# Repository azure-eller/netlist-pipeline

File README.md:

# netlist-pipeline

A KiCad schematic goes in. A fabrication-ready board comes out: placed by search, routed,
scored by a physics judge, verified by KiCad's own design-rule check, exported as Gerbers.
Every stage is a recorded job with a tool version, input hash and output hash, so any run can
be replayed. The judge is a slot: a learned physics model replaces the closed-form reference
behind one HTTP contract, and a golden set decides whether the worker accepts it.

## Architecture

```mermaid
flowchart LR
    client([client]) -->|POST /designs| api[api<br/>FastAPI]
    api --> pg[(Postgres<br/>designs, runs, jobs,<br/>stages, nets, candidates,<br/>verifications, artifacts)]
    api --> s3[(S3<br/>uploads, boards,<br/>reports, gerbers)]
    worker[worker<br/>kicad-cli, pcbnew,<br/>Freerouting] -->|claim job<br/>SKIP LOCKED| pg
    worker --> s3
    client -->|GET /runs/id| api
```

Two containers from one image, a managed Postgres, and a bucket. The API never does work that
takes more than a second: it writes a job row and the worker claims it. The worker runs the
eight stages one job at a time, and the judge stage calls a separate judge service over HTTP.
That service is the model slot.

<details>
<summary>Detailed architecture</summary>

</details>

**Stage 4, watched.** `GET /` on the API is a status board: one row per run, one cell per
stage, and while a run is in `place` it draws the annealer live, parts, rat's nest by net
class and the cost curve, from snapshots the stage writes every 0.1 % of its moves.

## The judge, and the physics model inside it

Everything in this section is about one question: **is this board electrically good?** A board
can have every wire connected and still be bad. This is what the judge measures, why part of
it had to be learned, and how we know the learned part is right.

### 1. What the judge does

After routing, the pipeline has up to ten candidate boards, all wired correctly. The judge
gives each one a score and the best one goes on to verification. The score is a penalty: zero
for a board that breaks no rule, more negative for every rule it breaks and for how badly.

| rule | in plain words | needs physics? |
|---|---|---|
| current | a power trace must be wide enough to carry its current without heating more than 10 °C | textbook formula (IPC-2221) |
| impedance | a high-speed trace must present the impedance the chip expects, 50 Ω by default, within 10 % | **yes** |
| diff pair | the two wires of a differential pair must be the same length within 1 mm | no |
| decoupling | a chip's decoupling capacitor must sit within 10 mm of the pin it serves | no |
| crosstalk | two traces must not run side by side for long stretches with a small gap | no |
| vias | a high-speed trace should change layers at most twice | no |
| unrouted | any connection the router gave up on | no |

Each broken rule costs its weight times how far past the limit it went. A 0.3 mm trace
asked to carry twice what it can costs more than one asked to carry 5 % more. Current and
impedance weigh most, because those are the ones that make a board not work rather than
merely not ideal.

The judge picks the best candidate. It never passes or fails a run; that is verify's job.

### 2. Impedance, and why it is the hard rule

Six of the seven rules are geometry you can measure with a ruler: distance, length, width,
count. Impedance is different.

A fast signal on a trace does not behave like water in a pipe, it behaves like a wave on a
rope. The trace has a characteristic impedance, measured in ohms, and if the chip at the far
end expects 50 Ω and the trace is 90 Ω, part of every edge bounces back and the signal is
corrupted. The impedance is set by four things: how wide the trace is (**w**), how far it sits
above the copper ground plane (**h**), how thick the copper is (**t**), and how strongly the
board material stores electric field, a number called relative permittivity (**er**, about
4.5 for ordinary FR-4 fibreglass). Wider or closer to the plane means lower impedance.

The judge needs this number for every high-speed trace on every candidate. So where does it
come from? That is a separate piece, the **physics provider**, and there are three of them.

### 3. Three ways to get the number

| provider | what it is | one answer takes |
|---|---|---|
| formula | the IPC-2141 closed form, a one-line equation from a standards handbook | a few microseconds |
| field solver | our own program that computes the electric field around the trace, alone or among its neighbours | 0.4 to 1.6 s |
| learned-fd v5 | gradient boosting trained to predict what the solver says for one trace over a plane | under a millisecond |
| learned-cut v8 | a small transformer that reads the whole slice, neighbours and all, and predicts the solver's capacitance matrix | a few milliseconds |

The same three traces through all three, single-ended impedance in ohms:

| trace | formula | field solver | learned-fd v5 |
|---|---|---|---|
| 0.2 mm wide, 1.51 mm above the plane (a signal trace on a plain 2-layer board) | 137.3 | 135.7 | 134.1 |
| 2.9 mm wide, same board (what 50 Ω needs on that board) | 48.1 | 49.1 | 49.1 |
| 0.35 mm wide, 0.2 mm above the plane (a 4-layer board) | 49.0 | 51.4 | 53.0 |

The first row is the finding from run 76: the I2C traces on the generated Raspberry Pi HAT are
0.2 mm wide over a 1.5 mm core, so they sit near 135 Ω against a 50 Ω target, and the judge
flagged both of them.

The formula is quick and usually close, but it is a curve fitted to measurements decades
ago, valid over a limited range of shapes, and it knows nothing about a neighbouring trace or
a missing plane. The field solver is the truth we have. The learned models exist because the
truth is slow.

The first three describe a slice with four numbers and assume a solid plane under the trace.
Boards this pipeline generates have no plane, and only 46 of the 5,206 slices cut from our
real boards do. The fourth provider reads the slice as it is: a list of conductors, each
with its width and distance, and whether a plane is there. Each conductor becomes a token, the
tokens attend to each other with their pairwise gaps built into the attention, and a
symmetric head reads off the full capacitance matrix, the object the solver itself computes.
Impedance and crosstalk coupling are derived from that matrix by the solver's own formula.
Trained on 8,000 synthetic slices plus the real slices of one board family, it predicts the
solver within 1.8 % on a board family it never saw, where gradient boosting on hand-made
features manages 3.5 %. The record, including the run that did not transfer, is in
[docs/experiments/cutnet.md](docs/experiments/cutnet.md).

### 4. The field solver, in plain words

"2D" means the solver never looks at the whole board. Impedance does not depend on how long a
trace is, only on its cross-section, so the solver takes one slice straight across the trace
and works entirely on that slice.

What happens on the slice:

1. **Divide it into a grid.** About 400 cells across and 200 up. Cells are small near the
   trace, where the field changes quickly, and grow larger out towards the edges where
   nothing much happens.
2. **Pin the known voltages.** The trace is held at 1 volt, the ground plane at 0.
3. **Find the voltage everywhere else.** In empty space, each point's voltage is the average of
   its neighbours; at the boundary between air and board material, the average is weighted by
   permittivity. That gives one equation per grid point, about 80,000 of them, all coupled.
   The solver writes them as one sparse matrix and solves it in one shot. The right panel
   above is the result: every grid point's voltage.
4. **Turn the field into capacitance.** A field stores energy, and the energy stored per metre
   of trace tells you the capacitance per metre between trace and plane.
5. **Do it twice.** Once with the real board material and once with the board replaced by air.
   Impedance is set by the two capacitances together, and that pair also gives the speed the
   signal travels at.

For a pair of traces it does the same with the second trace held at +1 V and then at −1 V,
which is what differential pairs and crosstalk need.

The solver was checked against the Hammerstad-Jensen equations, the most trusted closed form
for this shape, and its impedance agrees within 1 % across the range where that form is valid. It takes
about 0.4 s per slice. A board with a dozen high-speed nets, ten candidates, and a search
that wants to score thousands of layouts cannot afford that.

### 5. Teaching a model to imitate the solver

The pattern is: a slow, trusted source of answers produces a dataset; a fast model learns it;
the fast model is checked against the slow one before it is allowed near a real board.

**The dataset.** 5,000 random cross-sections were drawn from the ranges real boards use, and
the solver answered every one. The draws are logarithmic, so thin traces and thin dielectrics,
where impedance changes fastest, are not starved of examples.

| input | range |
|---|---|
| trace width w | 0.1 to 2.0 mm |
| height above plane h | 0.08 to 1.6 mm |
| copper thickness t | 0.018, 0.035 or 0.070 mm, the three foils fabs stock |
| permittivity er | 3.0 to 4.8 |
| gap to a partner trace s | 0.1 to 3.0 mm, present in half the samples |

The work went through the same job queue that builds boards: four jobs of 1,250 slices each,
about two minutes per job on 16 cores. The result is dataset 17: four files plus a manifest
naming the sampler version, solver version and random seed, with the sha256 of every file. The
random seed means the exact same 5,000 slices can be regenerated from scratch.

**The model.** Gradient boosting: 600 small decision trees, each one trained to correct the
mistakes of all the trees before it. The inputs are the four (or five) numbers above, given
to the trees as logarithms, because impedance behaves logarithmically in width and height and
that makes the job easier. There are two models in the artifact: one for single traces
predicting z0, one for pairs predicting the odd- and even-mode impedances that differential
pairs and crosstalk are built from. Training plus the check below took 81 s.

**The first check.** 20 % of the dataset was held back from training and scored afterwards:
0.9 % average error on single-trace impedance. Then 200 brand-new slices were drawn after
training was finished and solved by the solver, so the model was tested on data that did not
exist when it was built:

| target | average error | 95th percentile |
|---|---|---|
| z0, single trace | 0.9 % | 2.4 % |
| z_odd, pair | 2.1 % | 4.2 % |
| z_even, pair | 1.7 % | 3.6 % |

The judge's impedance rule allows 10 %, so the model's error is a small fraction of the
tolerance it is judging against.

### 6. The gate: no model touches a board until it passes

Agreeing with the solver on random slices is not the same as agreeing on real boards. So
every judge version, the formula included, has to pass the **golden set** before the worker
will accept it: seven real boards with known verdicts. Two are deliberately broken copies of
the others, one with a capacitor moved 30 mm so it sits 93 mm from the pin it serves, and one with every +5V trace
thinned to 0.15 mm, and a judge must rank each broken board below its original. Two more
carry high-speed traces with copper, so the impedance rule is actually exercised. The expected
answers come from the field solver.

Three earlier learned judges, v2 through v4, were refused at this gate. They matched the
reference on the ordinary boards and under-penalised the far-capacitor board. They never
reached the worker. The record is in [docs/experiments](docs/experiments/README.md).

Passing writes a row in the `judge_approvals` table naming the judge's name, version, the
sha256 of its model file, and the sha256 of the golden set it passed. The `models` table
already holds the file's location, its dataset, its feature encoding, the library version and
the commit. Neither table can be edited, only added to. Then:

- the judge service loads the model file from S3, hashes the bytes, and refuses to start if the
  hash differs from the row;
- the worker's judge stage asks the service who it is and refuses the run unless that exact
  (name, version, file hash) has an approval row;
- every score the pipeline stores records which bytes produced it.

Swapping a model file, retraining under the same version number, or pointing the worker at an
unapproved judge all fail loudly.

### 7. What it does not know

- **One slice, one layer.** The general solver sees every conductor on the trace's own
  layer and a plane on the next, but not a trace on another layer, vias, or a plane with a
  hole in it. Boards this pipeline generates still have no ground pour, which is why the
  golden answer key had to be recomputed with real slices and why the formula and v5 now
  fail it.
- **No losses, no length.** Copper resistance and dielectric loss are ignored, and nothing
  depends on how long a trace is.
- **Only inside the box.** The model was trained on the ranges in the table above. Outside
  them it extrapolates, and the golden set is what catches that.
- **Simplified rules.** The judge charges nothing for total wire length; [docs/EVAL.md](docs/EVAL.md)
  shows search beating the human layout on this judge while using 73 % more copper.

[docs/FACTORY.md](docs/FACTORY.md) is the plan for the next step: labels from real board
geometry instead of random slices, so a model can learn what a neighbouring trace or a
missing plane does.

## Run it

```
make up && make migrate        # Postgres + MinIO
make api                       # FastAPI on :8000; GET / is a status board: runs, stages, the annealer live
make worker                    # the job loop
make demo                      # upload pic_programmer, poll, print the report
make check                     # ruff, mypy strict, unit tests, end-to-end suite
curl -F file=@project.zip 'http://localhost:8000/designs?mode=generate&seeds=3'
```

Needs KiCad 10 and Freerouting locally, or the Dockerfile. Live at
https://netlist-api-ivqr.onrender.com/healthz. Details in [docs/DEPLOY.md](docs/DEPLOY.md).

## Go deeper

- [SPEC.md](SPEC.md): the contract. Stages, constraints format, judge contract, invariants.
- [docs/JUDGE.md](docs/JUDGE.md): the judge slot, the approval gate, the field-solver oracle
  and the learned surrogate that passed it.
- [docs/FACTORY.md](docs/FACTORY.md): where a geometry model's labels would come from.
- [docs/EVAL.md](docs/EVAL.md): search versus the human layout on the fixtures.
- [docs/DECISIONS.md](docs/DECISIONS.md): what was not built and why. No language model runs
  in the pipeline; Claude built the repo.
- [docs/experiments](docs/experiments/README.md): every judge and placer experiment, with
  the ones that failed.

## How work gets done here

Cards on the Linear board labelled `agent` are picked up by OpenHands, self-hosted on
the lab machine, in a container built from this repo's image; the result is a pull
request with the link back on the card. This repo provides only `AGENTS.md` (the rules every
agent reads) and `make sandbox-image`; the lane itself, what was bought and what was built, and
why research is run differently are in the separate
[agent-lane](https://github.com/azure-eller/agent-lane) repo.

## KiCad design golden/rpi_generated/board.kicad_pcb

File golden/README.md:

# Golden set

Boards with expected scorecards for gating judge versions (SPEC.md, "Judge versions and
approval"). Built by `scripts/golden.py --capture` from local runs; rerunning overwrites.
`expected.json` is the rule judge's answer (regression and disagreement, not ground truth).

| case | board | netlist / constraints | expected (rules 0.1.0) |
|---|---|---|---|
| `pic_human` | `tests/fixtures/pic_programmer/pic_programmer.kicad_pcb`, the human layout | latest local judge-mode run of pic_programmer | -6.48; 3 decoupling (C1 on VCC, C6 and C7 on VCC_PIC) |
| `pic_generated` | chosen candidate of local generate run 34 (3 seeds) | same as `pic_human` | -1.20; decoupling C1, current on VCC_PIC |
| `rpi_generated` | chosen candidate of local generate run 27 (rpi_hat) | run 27 | -3.43; 2 current (+5V, GND) |
| `pic_cap_far` | `pic_human` with C1 moved 30 mm right of U1 (`pcb.set_positions`) | same as `pic_human` | -16.12; same 3 decoupling, C1 now ~93 mm from the nearest VCC pin. Must score below `pic_human`. |
| `rpi_thin` | `rpi_generated` with every `+5V` segment width set to 0.15 mm (text edit) | run 27 | -4.99; same 2 current violations, +5V excess larger. Must score below `rpi_generated`. |

Note: C1 already violates decoupling in the human layout (11.8 mm from U3 pin 5 on VCC; U1
carries no VCC pad), and the one `+5V` segment on the HAT already violates current at 0.2 mm.
The two mutated cases therefore worsen an existing violation rather than adding one; the
ordering constraints are what the gate checks.

## Impedance-live cases (added 2026-09-08)

The five original cases never exercise the impedance rule: the fixtures' fast nets carry no
copper. Two cases fix that, both on the generated HAT board with its routed I2C nets declared
`high_speed`:

- `rpi_fast`: target 50 ohm. A 0.2 mm trace over 1.51 mm FR-4 is far from 50 ohm, so both
  nets violate under every provider; the score depends on the provider's z0 (oracle -20.58,
  closed form -20.88).
- `rpi_fast_tuned`: target set to the closed form's own answer for that geometry. The formula
  passes by construction; the oracle passes only if its z0 is within 10% of the formula's,
  which it is here. A surrogate that drifts fails this case first.

Expected answers for every case now come from the oracle (`scripts/golden.py --physics
oracle --update`); the closed form is measured against them like any other judge and passes.

## Answer key recaptured from the general solver (2026-09-09)

`scripts/golden.py --physics oracle --update` again, now with the impedance rule asking the
provider per real cross-section (`docs/FACTORY.md` step 2: neighbours, plane or not). The five
plane-less cases did not move. The two impedance-live cases did, because the generated HAT has
no plane under its I2C traces and the old key assumed one:

| case | old key (plane assumed) | new key (real cross-sections) |
|---|---|---|
| `rpi_fast` | -20.58 | -24.18 |
| `rpi_fast_tuned` | -3.43 | -4.16 |

Any judge that still assumes a plane (the closed form, `learned-fd v5`) is measured against
this key like any other; the ledger in `docs/experiments/golden.jsonl` records what happened.

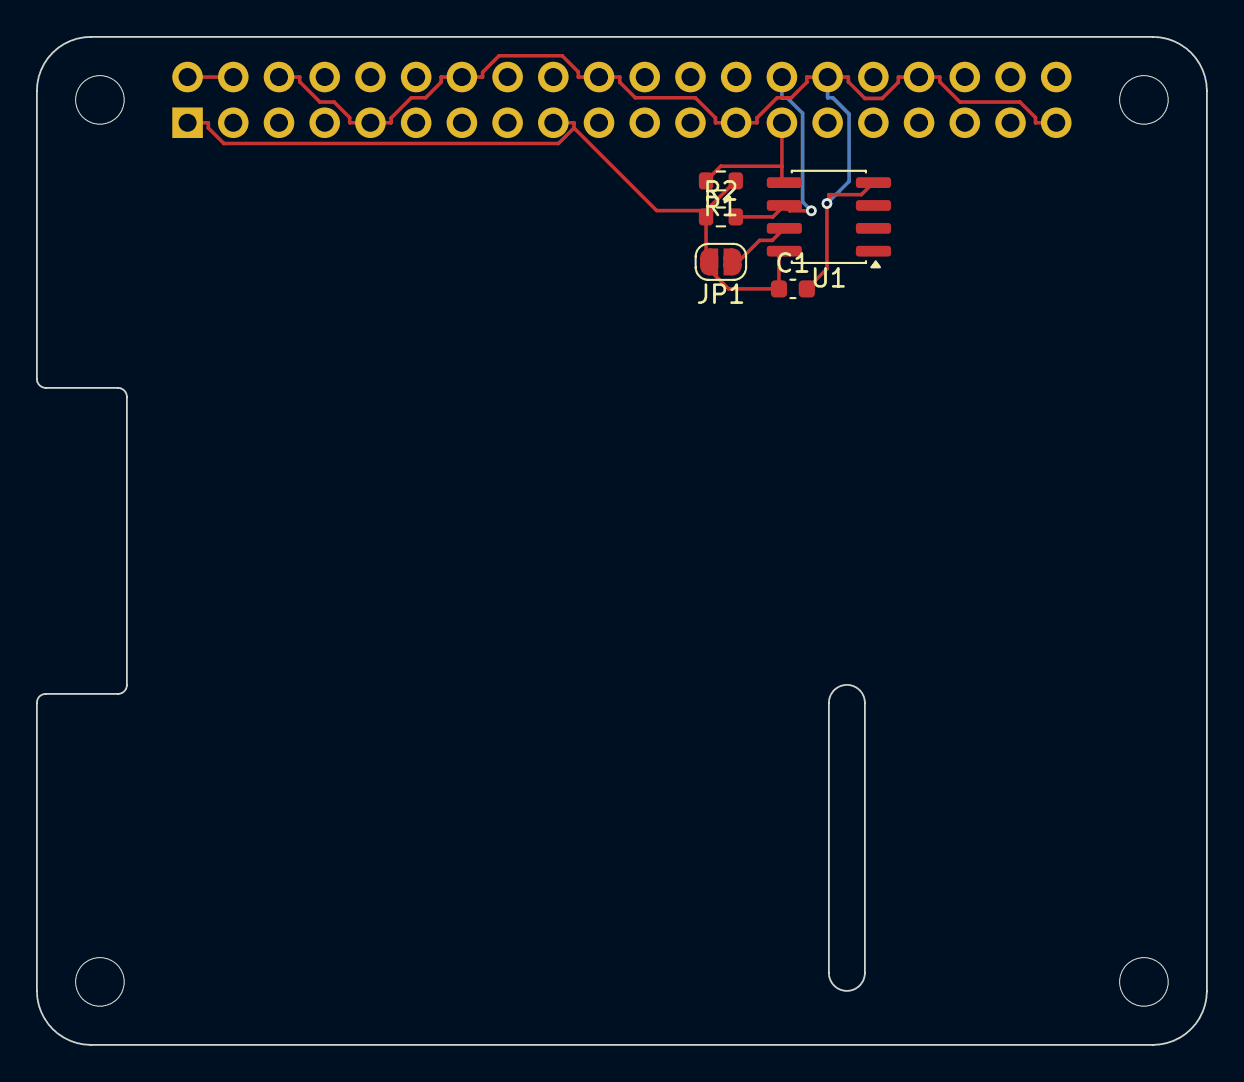
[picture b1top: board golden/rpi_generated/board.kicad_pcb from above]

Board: 2 copper layers, 65.0 x 56.0 mm, 10 parts (1 on the bottom side), 6 nets.

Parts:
C1: 100n; C_0603_1608Metric
J1: GPIO; PinSocket_2x20_P2.54mm_Vertical
JP1: ID_WP; SolderJumper-2_P1.3mm_Open_RoundedPad1.0x1.5mm
MH1, MH2, MH3, MH4: MountingHole_2.7mm_M2.5
R1, R2: 3.9k; R_0603_1608Metric
U1: CAT24C256; SOIC-8_3.9x4.9mm_P1.27mm

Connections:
+3V3: C1.1, J1.1, J1.17, JP1.2, R1.1, R2.1, U1.8
+5V: J1.2, J1.4
/ID_SCL: J1.28, R2.2, U1.6
/ID_SDA: J1.27, R1.2, U1.5
GND: C1.2, J1.6, J1.9, J1.14, J1.20, J1.25, J1.30, J1.34, J1.39, U1.4
unnamed: JP1.1, U1.7

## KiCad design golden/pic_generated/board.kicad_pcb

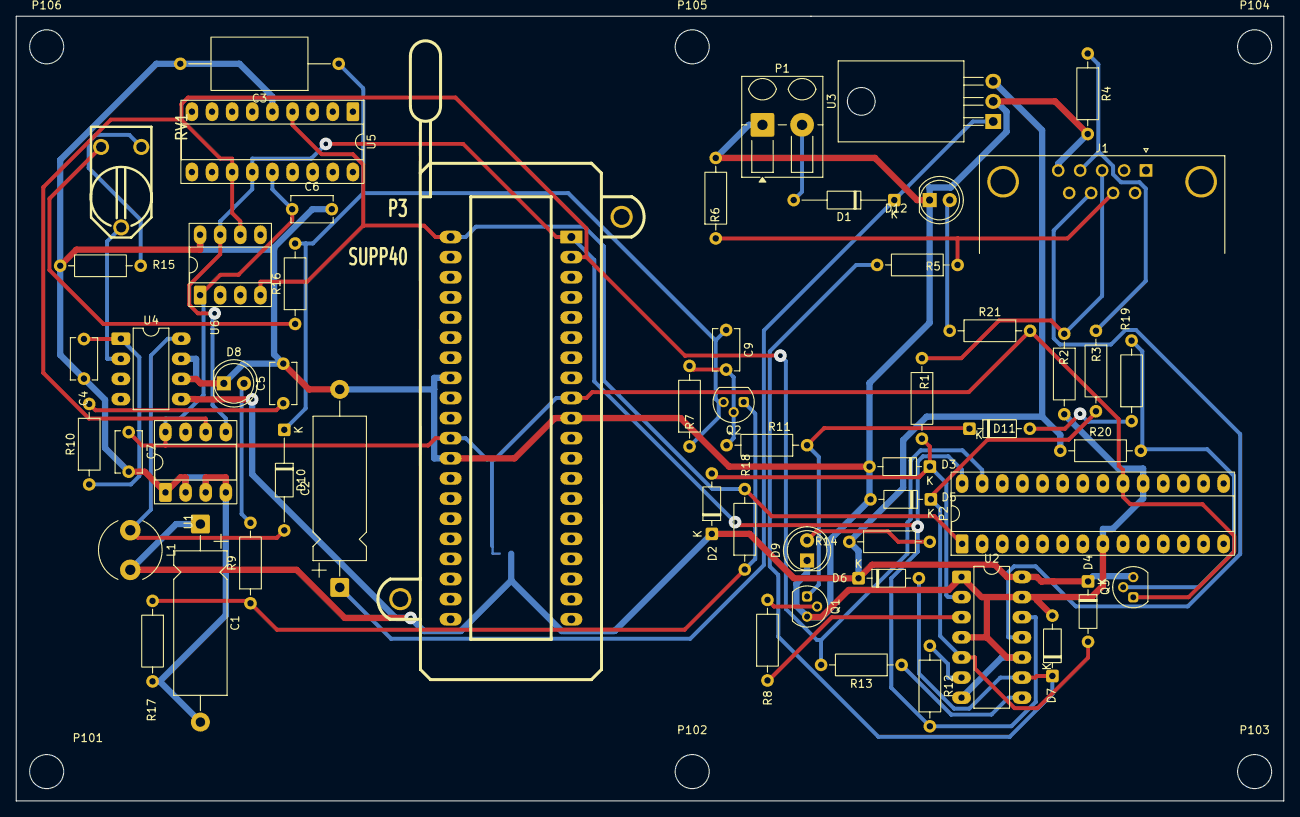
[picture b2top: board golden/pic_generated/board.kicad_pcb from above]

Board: 2 copper layers, 160.0 x 99.1 mm, 63 parts (1 on the bottom side), 34 nets.

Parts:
C1: 100µF; CP_Axial_L18.0mm_D6.5mm_P25.00mm_Horizontal
C2: 220uF; CP_Axial_L18.0mm_D6.5mm_P25.00mm_Horizontal
C3: 22uF/25V; C_Axial_L12.0mm_D6.5mm_P20.00mm_Horizontal
C4: 0; C_Disc_D5.1mm_W3.2mm_P5.00mm
C5: 10nF; C_Disc_D5.1mm_W3.2mm_P5.00mm
C6, C7: 100nF; C_Disc_D5.1mm_W3.2mm_P5.00mm
C9: 220nF; C_Disc_D5.1mm_W3.2mm_P5.00mm
D1: 1N4004; D_DO-35_SOD27_P12.70mm_Horizontal
D2, D3, D4, D5, D6, D7, D11: BAT43; D_DO-35_SOD27_P7.62mm_Horizontal
D8: RED-LED; LED_D5.0mm
D9: GREEN-LED; LED_D5.0mm
D10: SCHOTTKY; D_DO-35_SOD27_P12.70mm_Horizontal
D12: YELLOW-LED; LED_D5.0mm
J1: DB9-FEMAL; DSUB-9_Socket_Horizontal_P2.77x2.84mm_EdgePinOffset7.70mm_H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
JP1: JUMPER; SolderJumper-2_P1.3mm_Open_TrianglePad1.0x1.5mm
L1: 22uH; L_Radial_D7.8mm_P5.00mm_Fastron_07HCP
P1: CONN_2; Altech_AK300_1x02_P5.00mm_45-Degree
P2: SUPP28; DIP-28_W7.62mm_Socket_LongPads
P3: SUPP40; 40tex-Ell600
P101, P102, P103, P104, P105, P106: CONN_1; MountingHole_4.3mm_M4
Q1: BC237; TO-92
Q2, Q3: BC307; TO-92
R1, R2, R3, R4, R5, R6, R7: 10K; R_Axial_DIN0207_L6.3mm_D2.5mm_P10.16mm_Horizontal
R8: 1K; R_Axial_DIN0207_L6.3mm_D2.5mm_P10.16mm_Horizontal
R9, R19, R20: 2.2K; R_Axial_DIN0207_L6.3mm_D2.5mm_P10.16mm_Horizontal
R10: 5,1K; R_Axial_DIN0207_L6.3mm_D2.5mm_P10.16mm_Horizontal
R11, R17: 22K; R_Axial_DIN0207_L6.3mm_D2.5mm_P10.16mm_Horizontal
R12, R13, R14, R21: 470; R_Axial_DIN0207_L6.3mm_D2.5mm_P10.16mm_Horizontal
R15: 6.2K; R_Axial_DIN0207_L6.3mm_D2.5mm_P10.16mm_Horizontal
R16: 62K; R_Axial_DIN0207_L6.3mm_D2.5mm_P10.16mm_Horizontal
R18: 220; R_Axial_DIN0207_L6.3mm_D2.5mm_P10.16mm_Horizontal
RV1: 1K; RV2X4
U1: 24Cxx; DIP-8_W7.62mm_Socket_LongPads
U2: 74HC125; DIP-14_W7.62mm_LongPads
U3: 7805; TO-220-3_Horizontal_TabDown
U4: LT1373; DIP-8_W7.62mm_LongPads
U5: PIC_18_PINS; DIP-18_W7.62mm_Socket_LongPads
U6: PIC_8_PINS; DIP-8_W7.62mm_Socket_LongPads

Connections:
/CLOCK-RB6: P2.27, P3.39, R13.2, U1.6 (SCL), U5.12 (ICSPC/RB6), U6.6 (GP1)
/DATA-RB7: P2.28, P3.40, R12.2, U1.5 (SDA), U2.12, U5.13 (ICSPD/RB7), U6.7 (GP0)
/PC-CLOCK-OUT: J1.7, R5.1, R6.1
/PC-DATA-IN: J1.8, U2.11
/PC-DATA-OUT: J1.4, R3.1, R4.1
/VPP_ON: J1.3, R1.1, R2.1
/VPP/MCLR: P2.1, P3.1, R18.2, U5.4 (MCLR), U6.4 (GP3/MCLR)
/pic_sockets/VCC_PIC: C6.1, C7.1, JP1.2, P2.20, P3.11, P3.32, Q3.1 (C), R21.2, U1.8 (VCC), U5.14 (VDD), U6.1 (VDD)
GND: C1.2, C2.2, C3.2, C4.2, C5.2, C6.2, C7.2, D3.2 (A), D5.2 (A), D7.2 (A), D8.1 (K), D9.1 (K), D12.1 (K), J1.5, P1.1, P2.8, P2.19, P3.8, P3.12, P3.31, Q1.3 (E), R2.2, R4.2, R6.2, R15.2, R17.2, U1.1 (A0), U1.2 (A1), U1.3 (A2), U1.4 (GND), U2.1, U2.4, U2.7 (GND), U2.10, U2.13, U3.2 (GND), U4.6 (GND_S), U4.7 (GND), U5.5 (VSS), U6.8 (VSS)
unnamed: C5.1, R10.2
unnamed: D1.2 (A), P1.2 (PM)
unnamed: C2.1, D1.1 (K), U3.1 (VI)
unnamed: D2.2 (A), D3.1 (K), R1.2, U2.2
unnamed: D4.2 (A), D5.1 (K), R3.2, U2.5
unnamed: D6.2 (A), D7.1 (K), R5.2, U2.9
unnamed: D8.2 (A), R9.2
unnamed: D9.2 (A), R14.2
unnamed: D10.2 (A), L1.1, U4.8 (Vsw)
unnamed: D11.2 (A), R19.1
unnamed: D11.1 (K), Q1.1 (C), R11.1
unnamed: D12.2 (A), R21.1
unnamed: Q1.2 (B), R8.2
unnamed: C9.2, Q2.2 (B), R7.2, R11.2
unnamed: Q2.1 (C), R9.1, R17.1, R18.1
unnamed: Q3.2 (B), R19.2, R20.2
unnamed: R8.1, U2.3
unnamed: R12.1, U2.6
unnamed: R13.1, U2.8
unnamed: R15.1, RV1.1
unnamed: R16.1, RV1.3
unnamed: RV1.2, U4.2 (FB+)
unnamed: C4.1, R10.1, U4.1 (Vc)
VCC: C1.1, D2.1 (K), D4.1 (K), D6.1 (K), JP1.1, L1.2, Q3.3 (E), R14.1, R20.1, U2.14 (VCC), U3.3 (VO), U4.5 (Vin)
VPP: C3.1, C9.1, D10.1 (K), Q2.3 (E), R7.1, R16.2
